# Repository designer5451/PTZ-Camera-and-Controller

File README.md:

This PTZ camera head uses two ESP32 microcontrollers connected via Ethernet on a standard network, communicating over a TCP connection. The controller acts as the client, while the camera head serves as the server. A PS4 controller connects to the control module via Bluetooth. The PTZ head can pan and tilt the camera and control zoom through a standard 2.5mm LANC interface.

Designed specifically for the Canon Vixia HF G30 camcorder, the PTZ head includes a servo to rotate the camera’s custom control knob. Although optimized for the Canon HF G30, it can work with other cameras that fit within its dimensions and support a standard LANC jack. However, only the Canon HF G30 can utilize the servo control for the custom knob.

The PTZ head’s PCB includes an optional slot for an extra stepper motor, which can be configured to adjust the camera lens manually if you know how to edit Fusion 360 files and the ESP32 program. The controller board program requires updates with the PTZ camera head's IP address and the PS4 controller’s Bluetooth MAC address at the beginning of the program.

To produce the two PCBs, I used JLCPCB, designing the boards in KiCad 8.0. I've attached the KiCad document, Gerber files, and a schematic screenshot. I soldered the components with a "PINECIL – Smart Mini Portable Soldering Iron (Version 2)" from [Pine64](https://pine64.com/product/pinecil-smart-mini-portable-soldering-iron/). The 3D-printed parts were designed in Fusion 360, and I’ve included the Fusion archive file along with all parts as STL files. I printed all of the 3d parts in PLA except for the to drive gears and the gear on the end of the servo which I printed in TPU.

To cushion the base of the controller, I used a hot glue gun to apply small drops, creating soft pads. I also added small glue balls  that I pushed into the controller's light holes to help diffuse the light.

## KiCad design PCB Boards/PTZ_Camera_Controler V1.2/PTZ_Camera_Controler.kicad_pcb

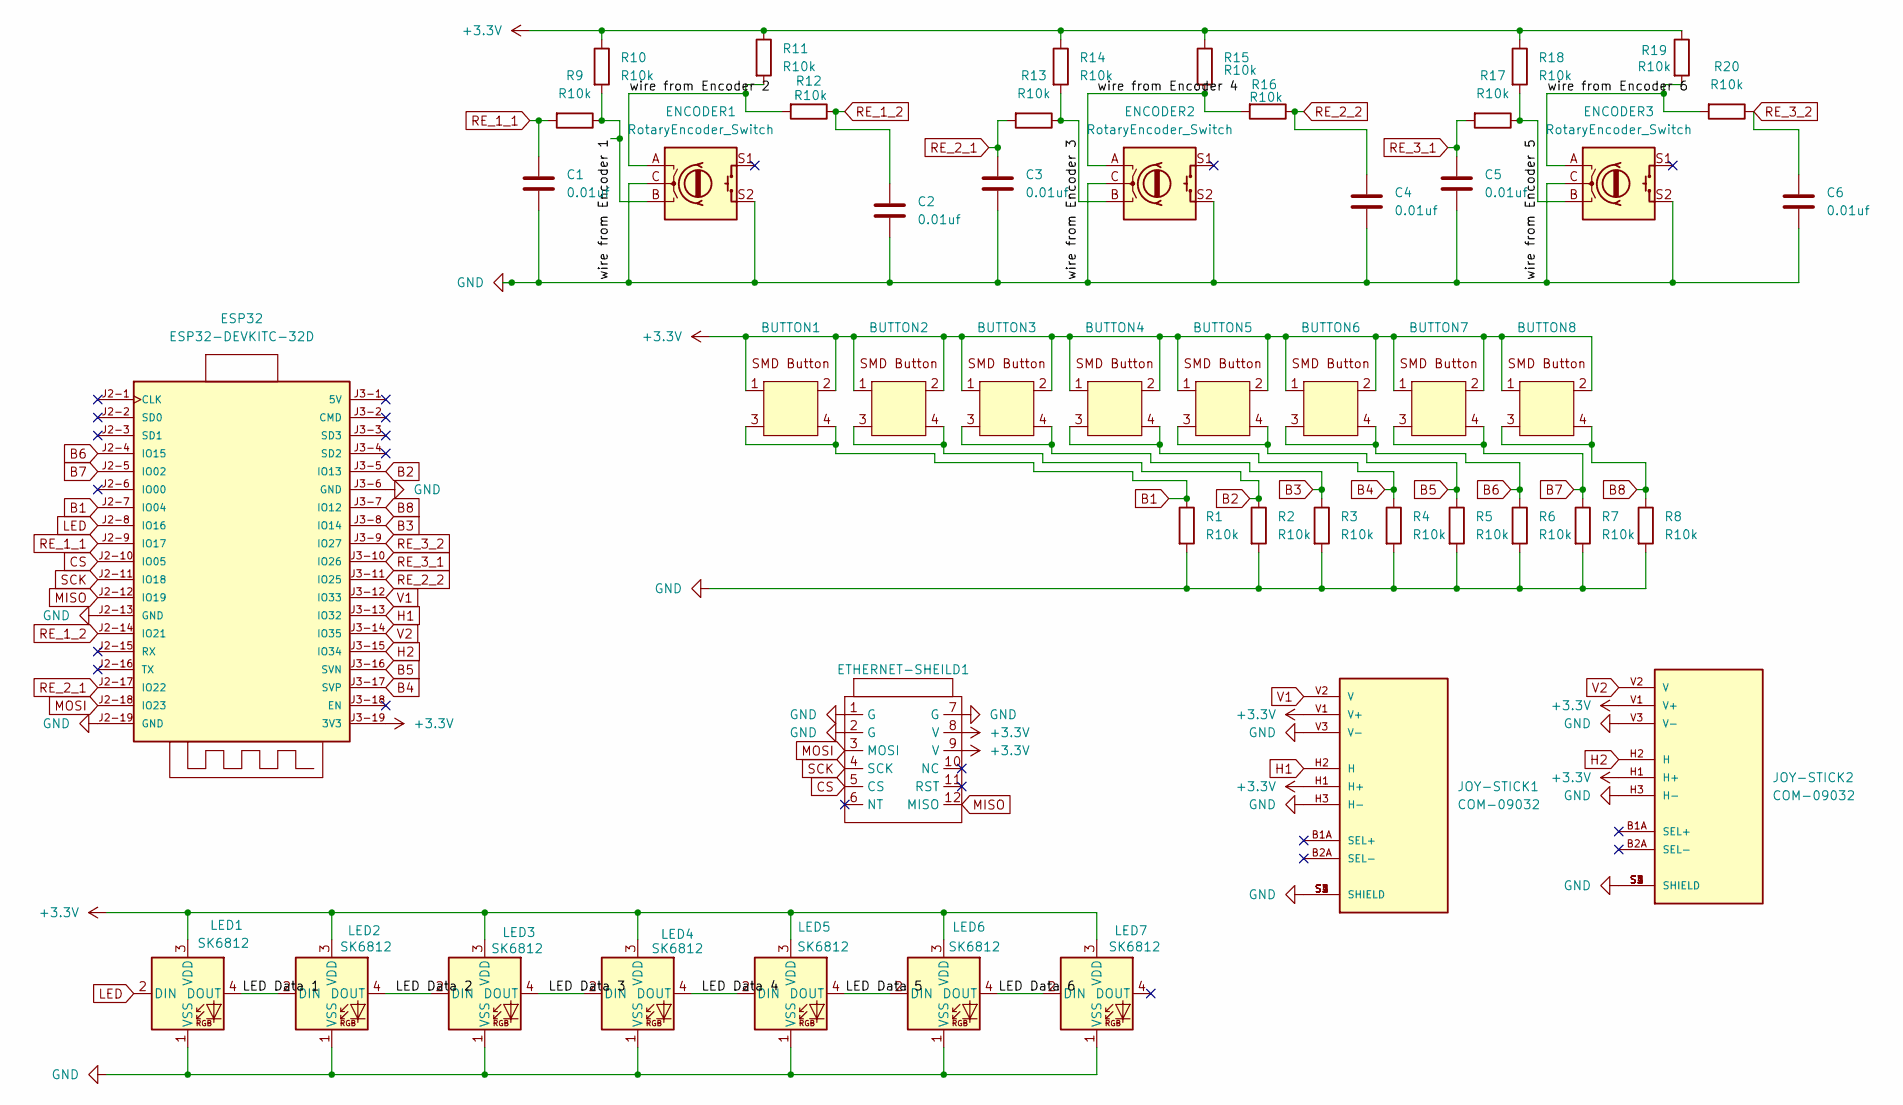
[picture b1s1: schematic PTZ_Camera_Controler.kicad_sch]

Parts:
BUTTON1, BUTTON2, BUTTON3, BUTTON4, BUTTON5, BUTTON6, BUTTON7, BUTTON8: TWS4417-250AT
C1, C2, C3, C4, C5, C6: 0.01uf; C_1206_3216Metric_Pad1.33x1.80mm_HandSolder
ENCODER1, ENCODER2, ENCODER3: RotaryEncoder_Switch; RotaryEncoder_Alps_EC11E-Switch_Vertical_H20mm
ESP32: ESP32-DEVKITC-32D; MODULE_ESP32-DEVKITC-32D; PARTREV V4
ETHERNET-SHEILD1: W5500_mini_ethernet_sheild
JOY-STICK1, JOY-STICK2: COM-09032; PARTREV N/A
LED1, LED2, LED3, LED4, LED5, LED6, LED7: SK6812; LED_SK6812_PLCC4_5.0x5.0mm_P3.2mm
R1, R2, R3, R4, R5, R6, R7, R8, R9, R10, R11, R12, R13, R14, R15, R16, R17, R18, R19, R20: R10k; R_1206_3216Metric

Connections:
+3.3V: BUTTON1.1, BUTTON1.2, BUTTON2.1, BUTTON2.2, BUTTON3.1, BUTTON3.2, BUTTON4.1, BUTTON4.2, BUTTON5.1, BUTTON5.2, BUTTON6.1, BUTTON6.2, BUTTON7.1, BUTTON7.2, BUTTON8.1, BUTTON8.2, ESP32.J3-19 (3V3), ETHERNET-SHEILD1.8 (V), ETHERNET-SHEILD1.9 (V), JOY-STICK1.H1 (H+), JOY-STICK1.V1 (V+), JOY-STICK2.H1 (H+), JOY-STICK2.V1 (V+), LED1.3 (VDD), LED2.3 (VDD), LED3.3 (VDD), LED4.3 (VDD), LED5.3 (VDD), LED6.3 (VDD), LED7.3 (VDD), R10.1, R11.1, R14.1, R15.1, R18.1, R19.1
/LED Data 1: LED1.4 (DOUT), LED2.2 (DIN)
/LED Data 2: LED2.4 (DOUT), LED3.2 (DIN)
/LED Data 3: LED3.4 (DOUT), LED4.2 (DIN)
/LED Data 4: LED4.4 (DOUT), LED5.2 (DIN)
/LED Data 5: LED5.4 (DOUT), LED6.2 (DIN)
/LED Data 6: LED6.4 (DOUT), LED7.2 (DIN)
/wire from Encoder 1: ENCODER1.B, R9.1, R10.2
/wire from Encoder 2: ENCODER1.A, R11.2, R12.2
/wire from Encoder 3: ENCODER2.B, R13.1, R14.2
/wire from Encoder 4: ENCODER2.A, R15.2, R16.2
/wire from Encoder 5: ENCODER3.B, R17.1, R18.2
/wire from Encoder 6: ENCODER3.A, R19.2, R20.2
B1: BUTTON1.3, BUTTON1.4, ESP32.J2-7 (IO04), R1.1
B2: BUTTON2.3, BUTTON2.4, ESP32.J3-5 (IO13), R2.1
B3: BUTTON3.3, BUTTON3.4, ESP32.J3-8 (IO14), R3.1
B4: BUTTON4.3, BUTTON4.4, ESP32.J3-17 (SVP), R4.1
B5: BUTTON5.3, BUTTON5.4, ESP32.J3-16 (SVN), R5.1
B6: BUTTON6.3, BUTTON6.4, ESP32.J2-4 (IO15), R6.1
B7: BUTTON7.3, BUTTON7.4, ESP32.J2-5 (IO02), R7.1
B8: BUTTON8.3, BUTTON8.4, ESP32.J3-7 (IO12), R8.1
CS: ESP32.J2-10 (IO05), ETHERNET-SHEILD1.5 (CS)
GND: C1.2, C2.2, C3.2, C4.2, C5.2, C6.2, ENCODER1.C, ENCODER1.S2, ENCODER2.C, ENCODER2.S2, ENCODER3.C, ENCODER3.S2, ESP32.J2-13 (GND), ESP32.J2-19 (GND), ESP32.J3-6 (GND), ETHERNET-SHEILD1.1 (G), ETHERNET-SHEILD1.2 (G), ETHERNET-SHEILD1.7 (G), JOY-STICK1.H3 (H-), JOY-STICK1.S1 (SHIELD), JOY-STICK1.S2 (SHIELD), JOY-STICK1.S3 (SHIELD), JOY-STICK1.S4 (SHIELD), JOY-STICK1.V3 (V-), JOY-STICK2.H3 (H-), JOY-STICK2.S1 (SHIELD), JOY-STICK2.S2 (SHIELD), JOY-STICK2.S3 (SHIELD), JOY-STICK2.S4 (SHIELD), JOY-STICK2.V3 (V-), LED1.1 (VSS), LED2.1 (VSS), LED3.1 (VSS), LED4.1 (VSS), LED5.1 (VSS), LED6.1 (VSS), LED7.1 (VSS), R1.2, R2.2, R3.2, R4.2, R5.2, R6.2, R7.2, R8.2
H1: ESP32.J3-13 (IO32), JOY-STICK1.H2 (H)
H2: ESP32.J3-15 (IO34), JOY-STICK2.H2 (H)
LED: ESP32.J2-8 (IO16), LED1.2 (DIN)
MISO: ESP32.J2-12 (IO19), ETHERNET-SHEILD1.12 (MISO)
MOSI: ESP32.J2-18 (IO23), ETHERNET-SHEILD1.3 (MOSI)
RE_1_1: C1.1, ESP32.J2-9 (IO17), R9.2
RE_1_2: C2.1, ESP32.J2-14 (IO21), R12.1
RE_2_1: C3.1, ESP32.J2-17 (IO22), R13.2
RE_2_2: C4.1, ESP32.J3-11 (IO25), R16.1
RE_3_1: C5.1, ESP32.J3-10 (IO26), R17.2
RE_3_2: C6.1, ESP32.J3-9 (IO27), R20.1
SCK: ESP32.J2-11 (IO18), ETHERNET-SHEILD1.4 (SCK)
V1: ESP32.J3-12 (IO33), JOY-STICK1.V2 (V)
V2: ESP32.J3-14 (IO35), JOY-STICK2.V2 (V)

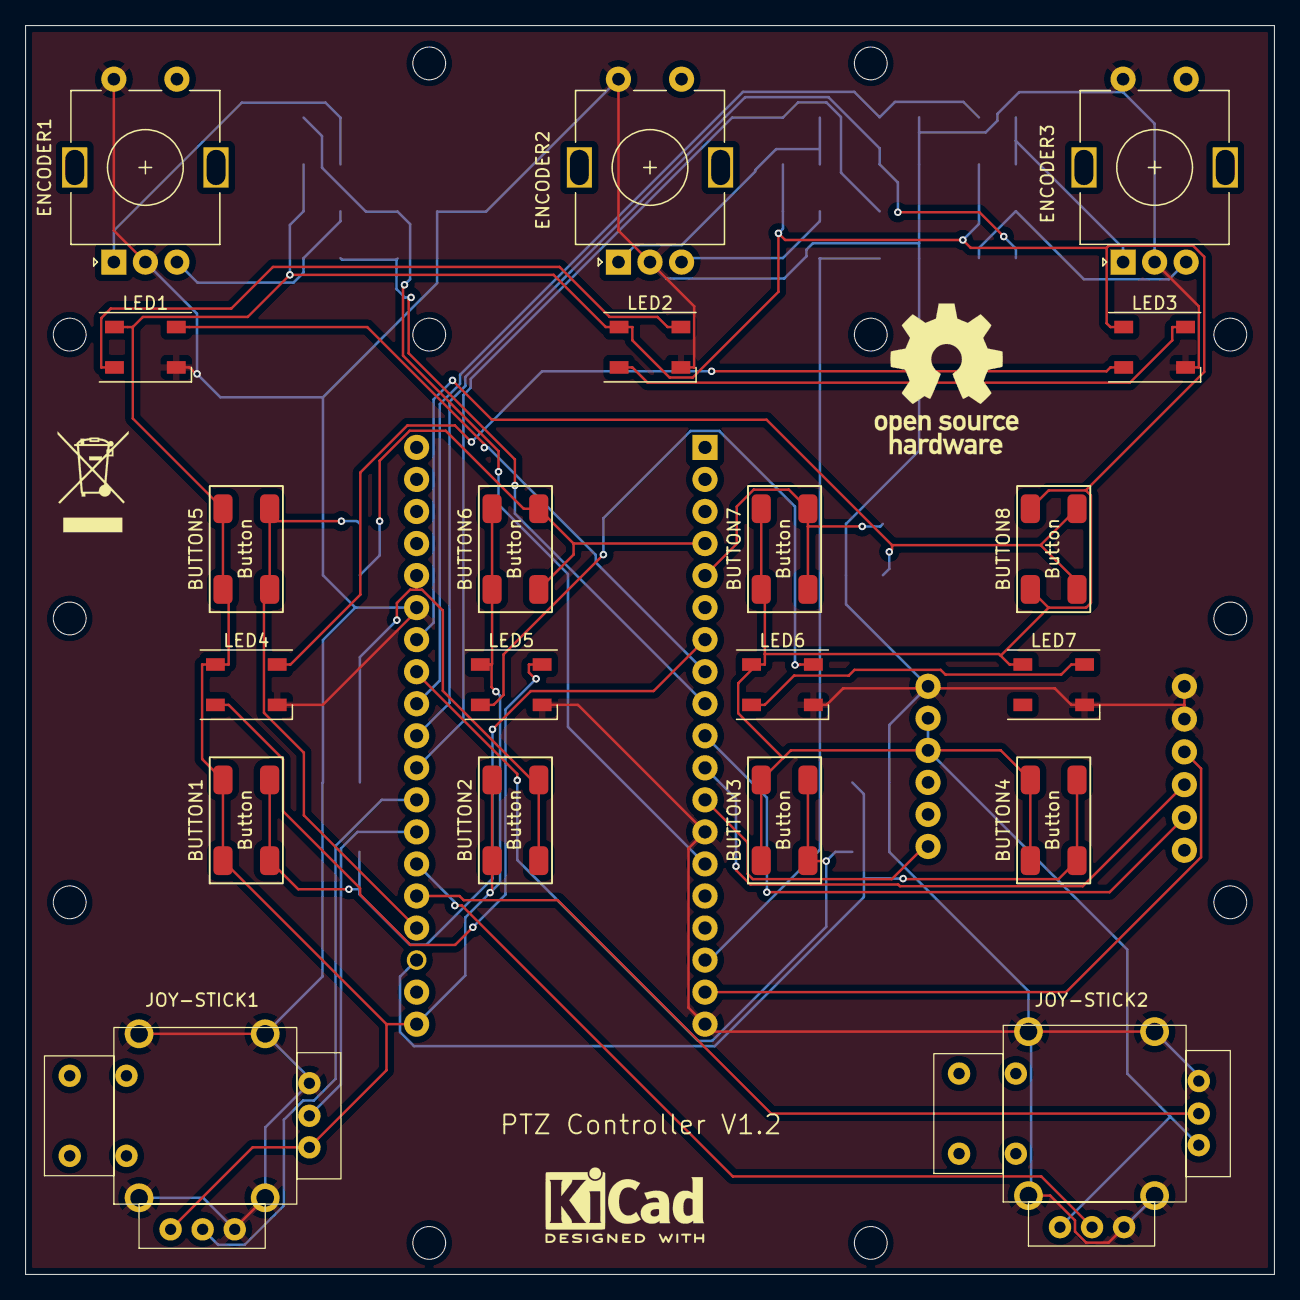
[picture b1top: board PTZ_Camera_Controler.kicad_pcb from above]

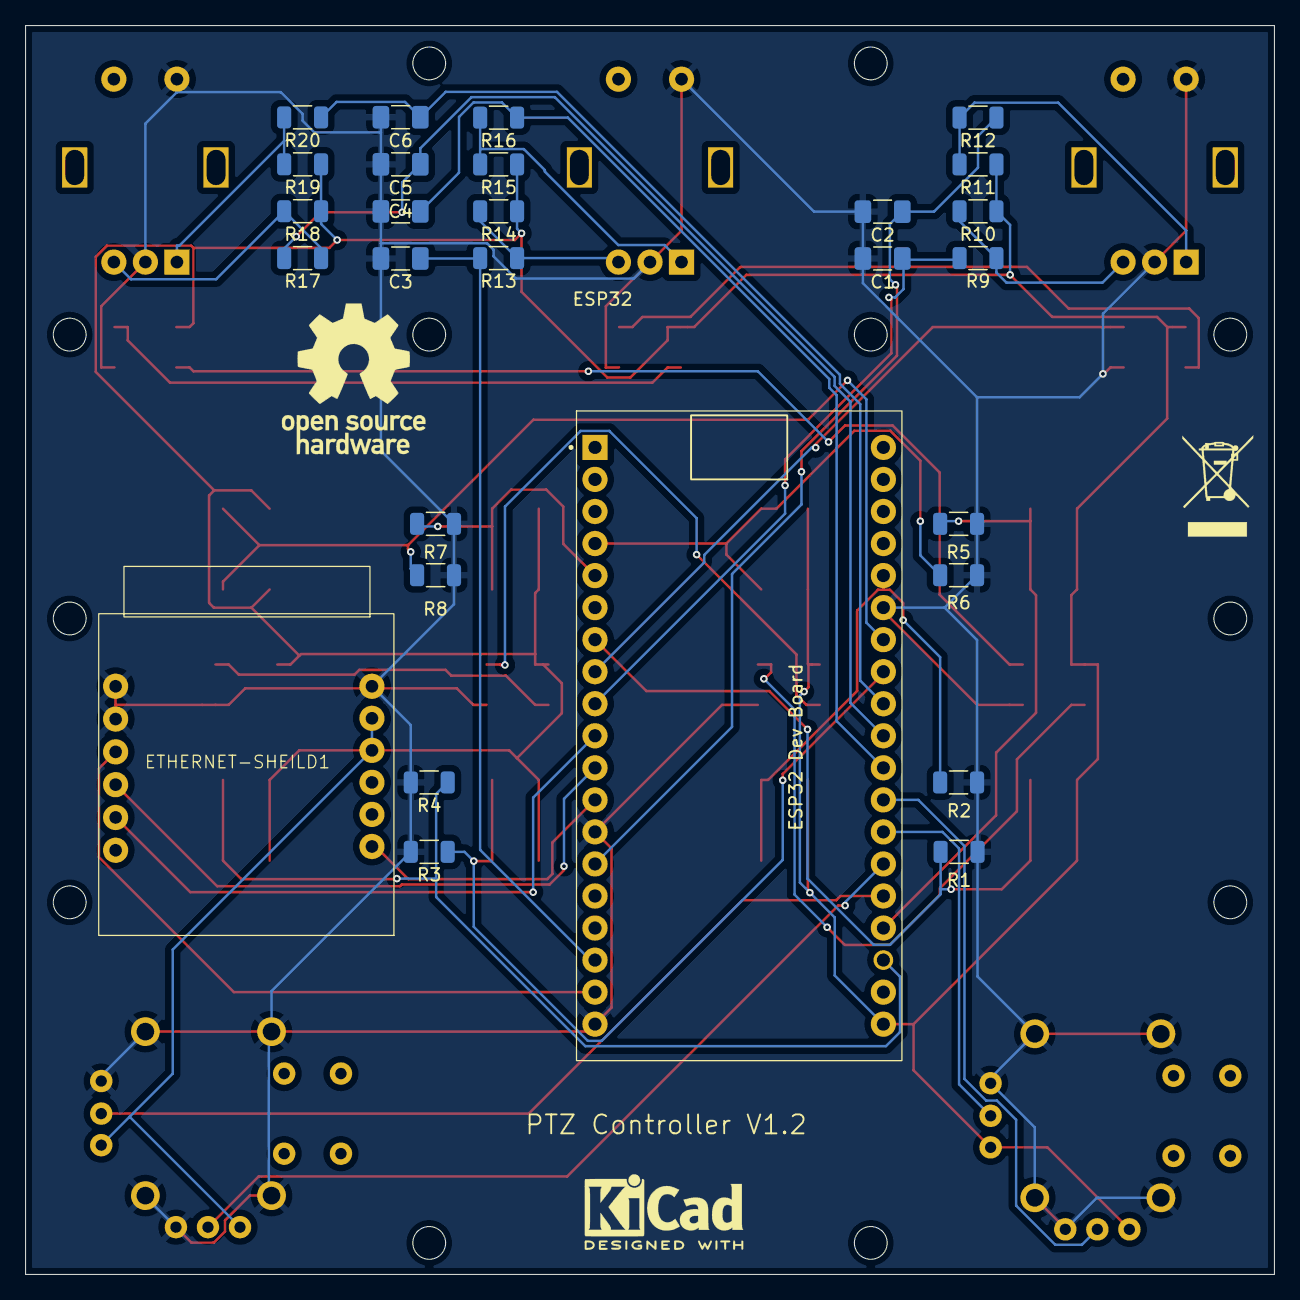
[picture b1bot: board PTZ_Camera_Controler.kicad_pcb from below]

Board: 2 copper layers, 99.0 x 99.0 mm, 54 parts (31 on the bottom side), 37 nets.

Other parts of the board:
REF1, REF2: KiCad-Logo2_5mm_SilkScreen
REF3, REF4: OSHW-Logo_11.4x12mm_SilkScreen
REF5, REF6: WEEE-Logo_5.6x8mm_SilkScreen

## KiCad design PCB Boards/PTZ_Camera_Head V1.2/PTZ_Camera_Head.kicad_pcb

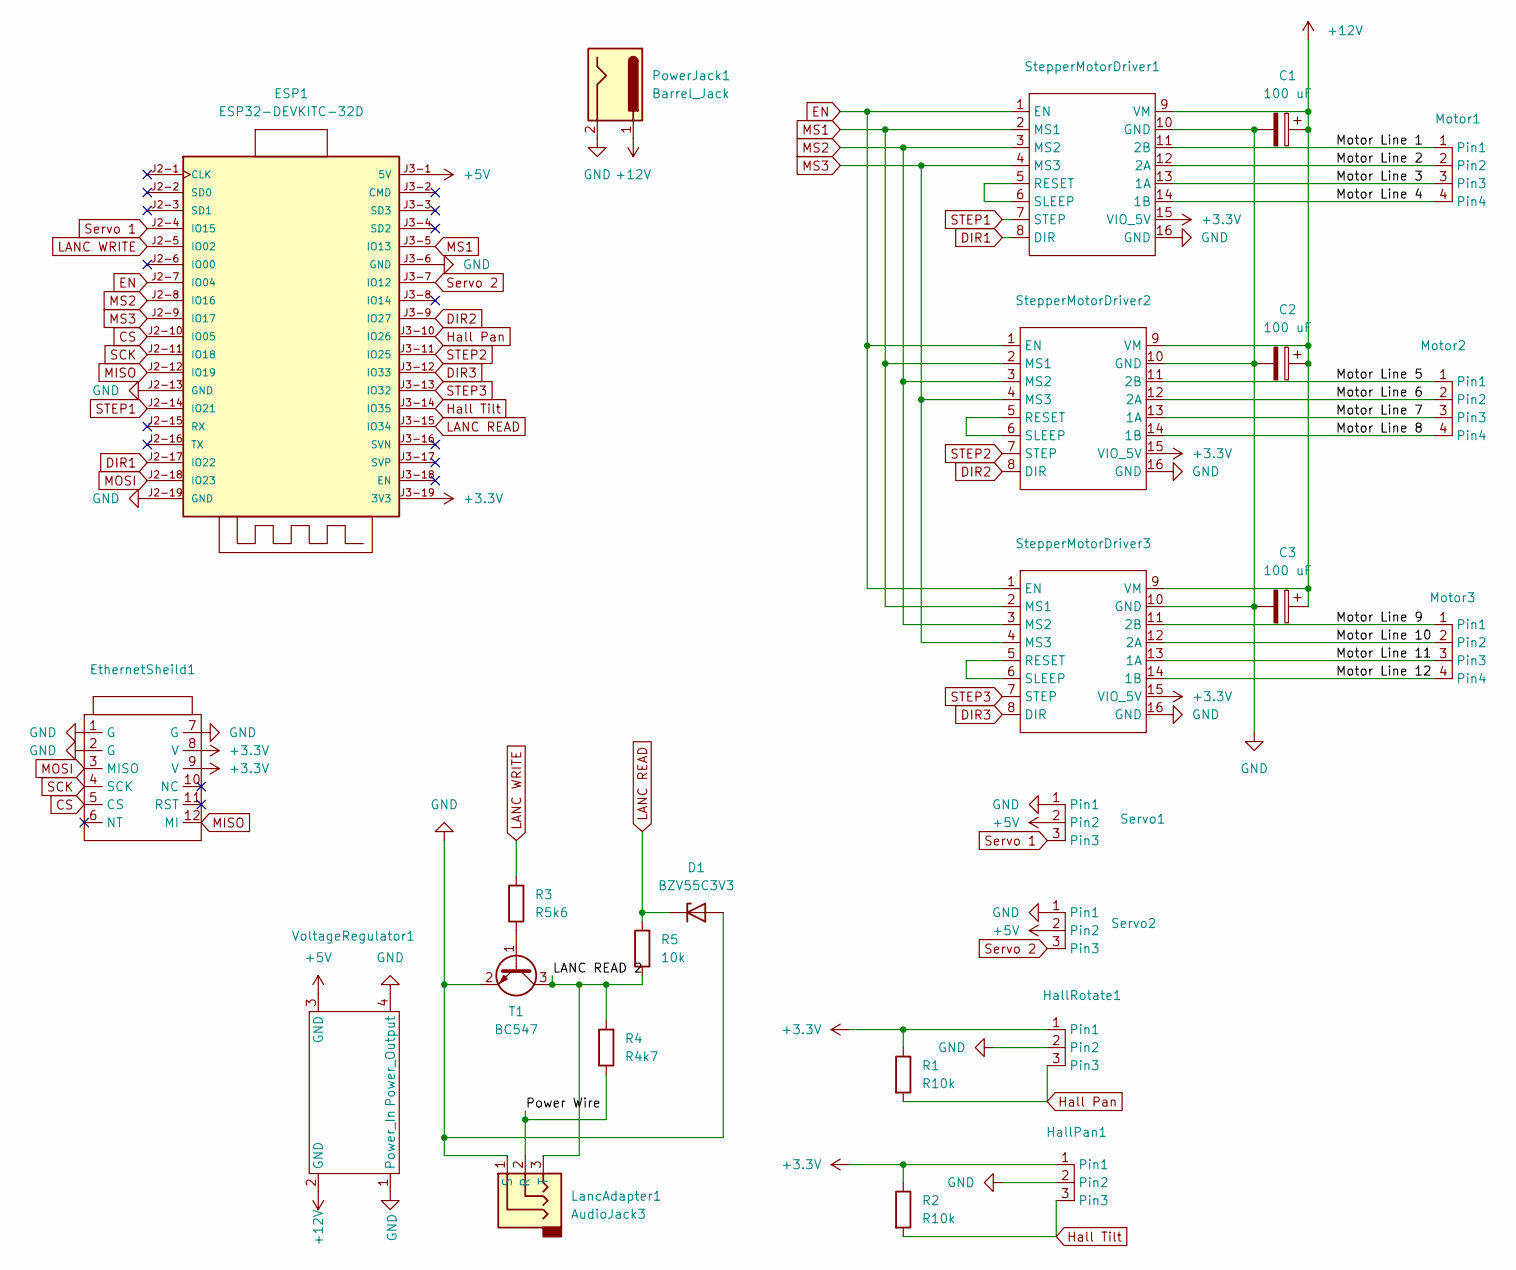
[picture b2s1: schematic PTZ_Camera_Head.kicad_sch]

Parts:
C1, C2, C3: 100 uF; CP_Radial_D5.0mm_P2.50mm
D1: BZV55C3V3; D_MiniMELF
ESP1: ESP32-DEVKITC-32D; MODULE_ESP32-DEVKITC-32D; PARTREV V4
EthernetSheild1: W5500_mini_ethernet_sheild
HallPan1: PinHeader_1x03_P2.54mm_Vertical
HallRotate1: PinHeader_1x03_P2.54mm_Vertical
LancAdapter1: AudioJack3; PinHeader_1x03_P2.54mm_Vertical
Motor1, Motor2, Motor3: PinHeader_1x04_P2.54mm_Vertical
PowerJack1: Barrel_Jack; BarrelJack_Wuerth_6941xx301002
R1, R2: R10k; R_1206_3216Metric
R3: R5k6; R_1206_3216Metric
R4: R4k7; R_1206_3216Metric
R5: 10k; R_1206_3216Metric
Servo1, Servo2: PinHeader_1x03_P2.54mm_Vertical
StepperMotorDriver1, StepperMotorDriver2, StepperMotorDriver3: MODULE_TMC2209_SILENTSTEPSTICK
T1: BC547; SOT-23_Handsoldering
VoltageRegulator1: voltage_regulator_17_12mm

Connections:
+3.3V: ESP1.J3-19 (3V3), EthernetSheild1.8 (V), EthernetSheild1.9 (V), HallPan1.1 (Pin1), HallRotate1.1 (Pin1), R1.1, R2.1, StepperMotorDriver1.15 (VIO_5V), StepperMotorDriver2.15 (VIO_5V), StepperMotorDriver3.15 (VIO_5V)
+5V: ESP1.J3-1 (5V), Servo1.2 (Pin2), Servo2.2 (Pin2), VoltageRegulator1.3 (GND)
+12V: C1.1, C2.1, C3.1, PowerJack1.1, StepperMotorDriver1.9 (VM), StepperMotorDriver2.9 (VM), StepperMotorDriver3.9 (VM), VoltageRegulator1.2 (GND)
/LANC READ 2: LancAdapter1.3 (T), R4.2, R5.1, T1.3 (C)
/Motor Line 1: Motor1.1 (Pin1), StepperMotorDriver1.11 (2B)
/Motor Line 2: Motor1.2 (Pin2), StepperMotorDriver1.12 (2A)
/Motor Line 3: Motor1.3 (Pin3), StepperMotorDriver1.13 (1A)
/Motor Line 4: Motor1.4 (Pin4), StepperMotorDriver1.14 (1B)
/Motor Line 5: Motor2.1 (Pin1), StepperMotorDriver2.11 (2B)
/Motor Line 6: Motor2.2 (Pin2), StepperMotorDriver2.12 (2A)
/Motor Line 7: Motor2.3 (Pin3), StepperMotorDriver2.13 (1A)
/Motor Line 8: Motor2.4 (Pin4), StepperMotorDriver2.14 (1B)
/Motor Line 9: Motor3.1 (Pin1), StepperMotorDriver3.11 (2B)
/Motor Line 10: Motor3.2 (Pin2), StepperMotorDriver3.12 (2A)
/Motor Line 11: Motor3.3 (Pin3), StepperMotorDriver3.13 (1A)
/Motor Line 12: Motor3.4 (Pin4), StepperMotorDriver3.14 (1B)
/Power Wire: LancAdapter1.2 (R), R4.1
CS: ESP1.J2-10 (IO05), EthernetSheild1.5 (CS)
DIR1: ESP1.J2-17 (IO22), StepperMotorDriver1.8 (DIR)
DIR2: ESP1.J3-9 (IO27), StepperMotorDriver2.8 (DIR)
DIR3: ESP1.J3-12 (IO33), StepperMotorDriver3.8 (DIR)
EN: ESP1.J2-7 (IO04), StepperMotorDriver1.1 (EN), StepperMotorDriver2.1 (EN), StepperMotorDriver3.1 (EN)
GND: C1.2, C2.2, C3.2, D1.2 (A), ESP1.J2-13 (GND), ESP1.J2-19 (GND), ESP1.J3-6 (GND), EthernetSheild1.1 (G), EthernetSheild1.2 (G), EthernetSheild1.7 (G), HallPan1.2 (Pin2), HallRotate1.2 (Pin2), LancAdapter1.1 (S), PowerJack1.2, Servo1.1 (Pin1), Servo2.1 (Pin1), StepperMotorDriver1.10 (GND), StepperMotorDriver1.16 (GND), StepperMotorDriver2.10 (GND), StepperMotorDriver2.16 (GND), StepperMotorDriver3.10 (GND), StepperMotorDriver3.16 (GND), T1.2 (E), VoltageRegulator1.1 (Power_In), VoltageRegulator1.4 (Power_Output)
Hall Pan: ESP1.J3-10 (IO26), HallRotate1.3 (Pin3), R1.2
Hall Tilt: ESP1.J3-14 (IO35), HallPan1.3 (Pin3), R2.2
LANC READ: D1.1 (K), ESP1.J3-15 (IO34), R5.2
LANC WRITE: ESP1.J2-5 (IO02), R3.2
MISO: ESP1.J2-12 (IO19), EthernetSheild1.12 (MI)
MOSI: ESP1.J2-18 (IO23), EthernetSheild1.3 (MISO)
MS1: ESP1.J3-5 (IO13), StepperMotorDriver1.2 (MS1), StepperMotorDriver2.2 (MS1), StepperMotorDriver3.2 (MS1)
MS2: ESP1.J2-8 (IO16), StepperMotorDriver1.3 (MS2), StepperMotorDriver2.3 (MS2), StepperMotorDriver3.3 (MS2)
MS3: ESP1.J2-9 (IO17), StepperMotorDriver1.4 (MS3), StepperMotorDriver2.4 (MS3), StepperMotorDriver3.4 (MS3)
unnamed: StepperMotorDriver1.5 (RESET), StepperMotorDriver1.6 (SLEEP)
unnamed: StepperMotorDriver2.5 (RESET), StepperMotorDriver2.6 (SLEEP)
unnamed: StepperMotorDriver3.5 (RESET), StepperMotorDriver3.6 (SLEEP)
unnamed: R3.1, T1.1 (B)
SCK: ESP1.J2-11 (IO18), EthernetSheild1.4 (SCK)
STEP1: ESP1.J2-14 (IO21), StepperMotorDriver1.7 (STEP)
STEP2: ESP1.J3-11 (IO25), StepperMotorDriver2.7 (STEP)
STEP3: ESP1.J3-13 (IO32), StepperMotorDriver3.7 (STEP)
Servo 1: ESP1.J2-4 (IO15), Servo1.3 (Pin3)
Servo 2: ESP1.J3-7 (IO12), Servo2.3 (Pin3)

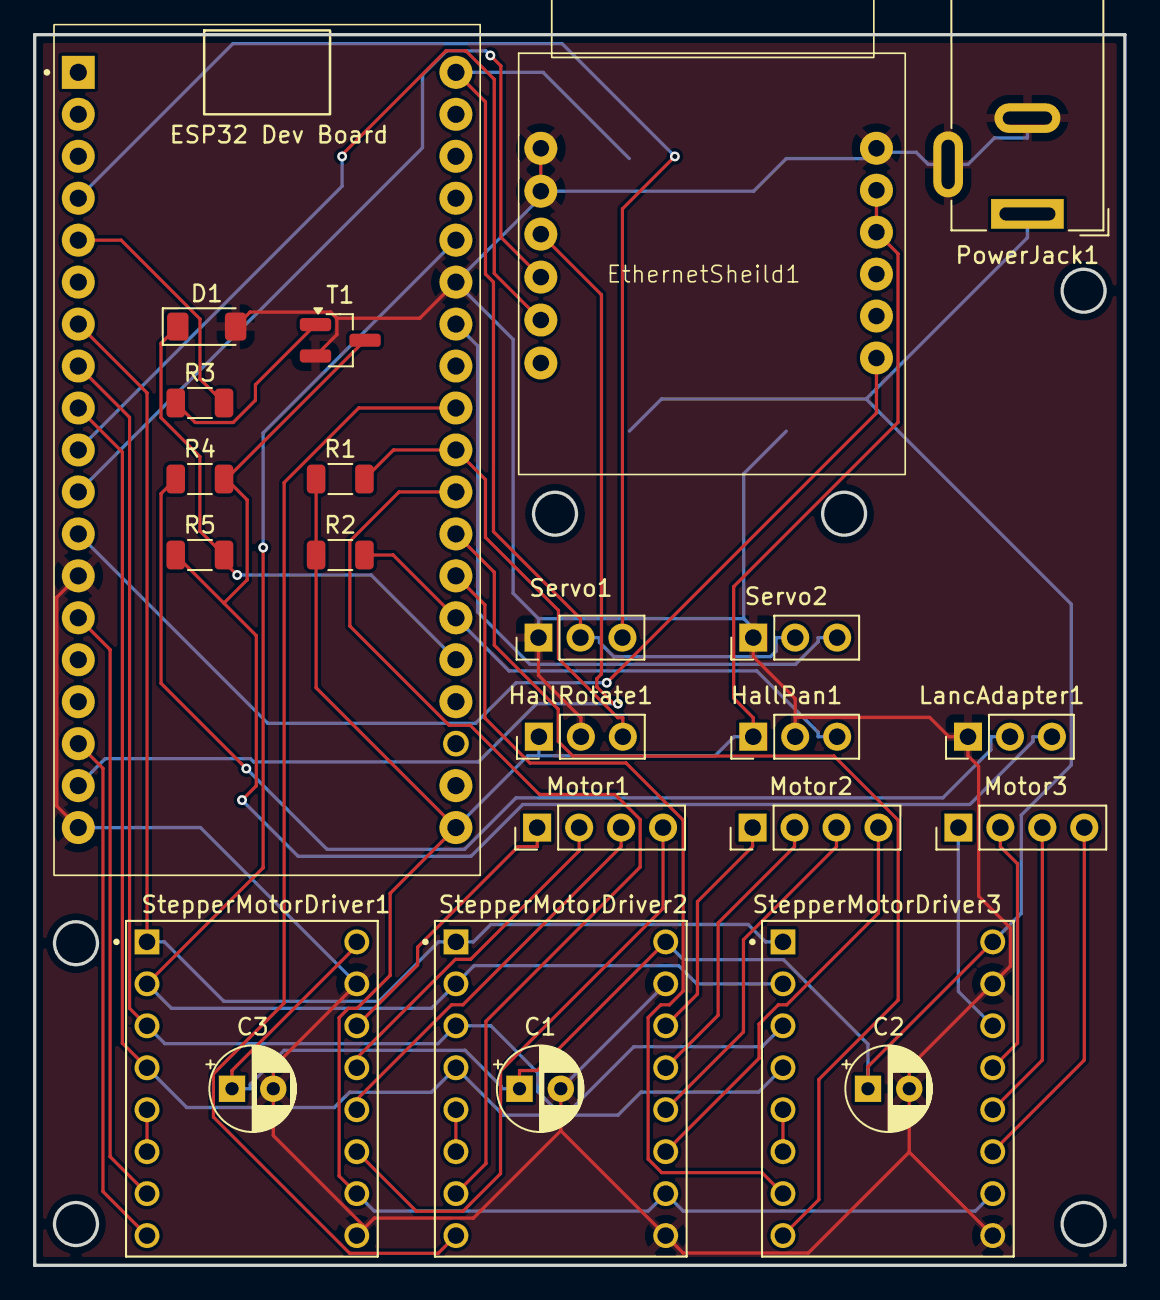
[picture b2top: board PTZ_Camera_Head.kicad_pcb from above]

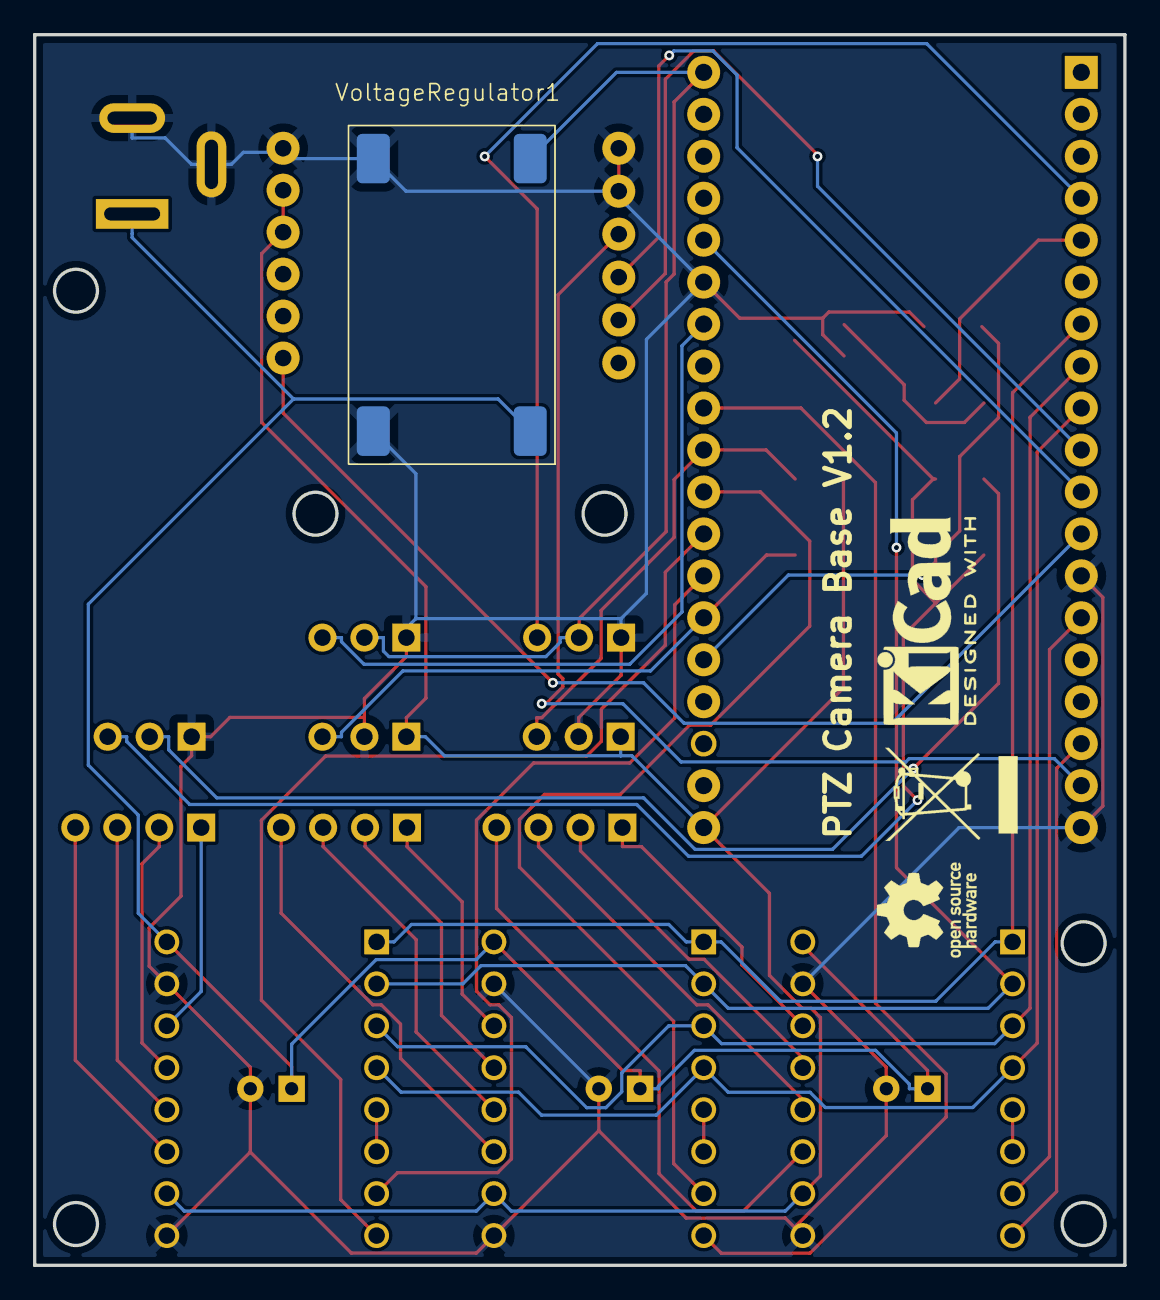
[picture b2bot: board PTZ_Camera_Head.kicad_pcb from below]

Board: 2 copper layers, 66.0 x 74.5 mm, 27 parts (3 on the bottom side), 42 nets.

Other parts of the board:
REF2: OSHW-Logo_5.7x6mm_SilkScreen
REF3: WEEE-Logo_5.6x8mm_SilkScreen

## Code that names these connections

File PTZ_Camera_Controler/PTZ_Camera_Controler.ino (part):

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#define Joypin1y 32
#define Joypin2x 35
#define Joypin2y 34
#define RE_1_1 17

#define RE_1_2 21
#define RE_2_1 22
#define RE_2_2 25
#define RE_3_1 26
#define RE_3_2 27

#define NUM_LEDS 7

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
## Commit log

2024-11-11 Update LICENSE
2024-11-11 Added Files
2024-11-11 Uploaded Pictures of PCB Schematics
2024-11-11 moved files
2024-11-25 Fix preset not working and inverted ps4 joysticks
2024-11-25 removed unused files
